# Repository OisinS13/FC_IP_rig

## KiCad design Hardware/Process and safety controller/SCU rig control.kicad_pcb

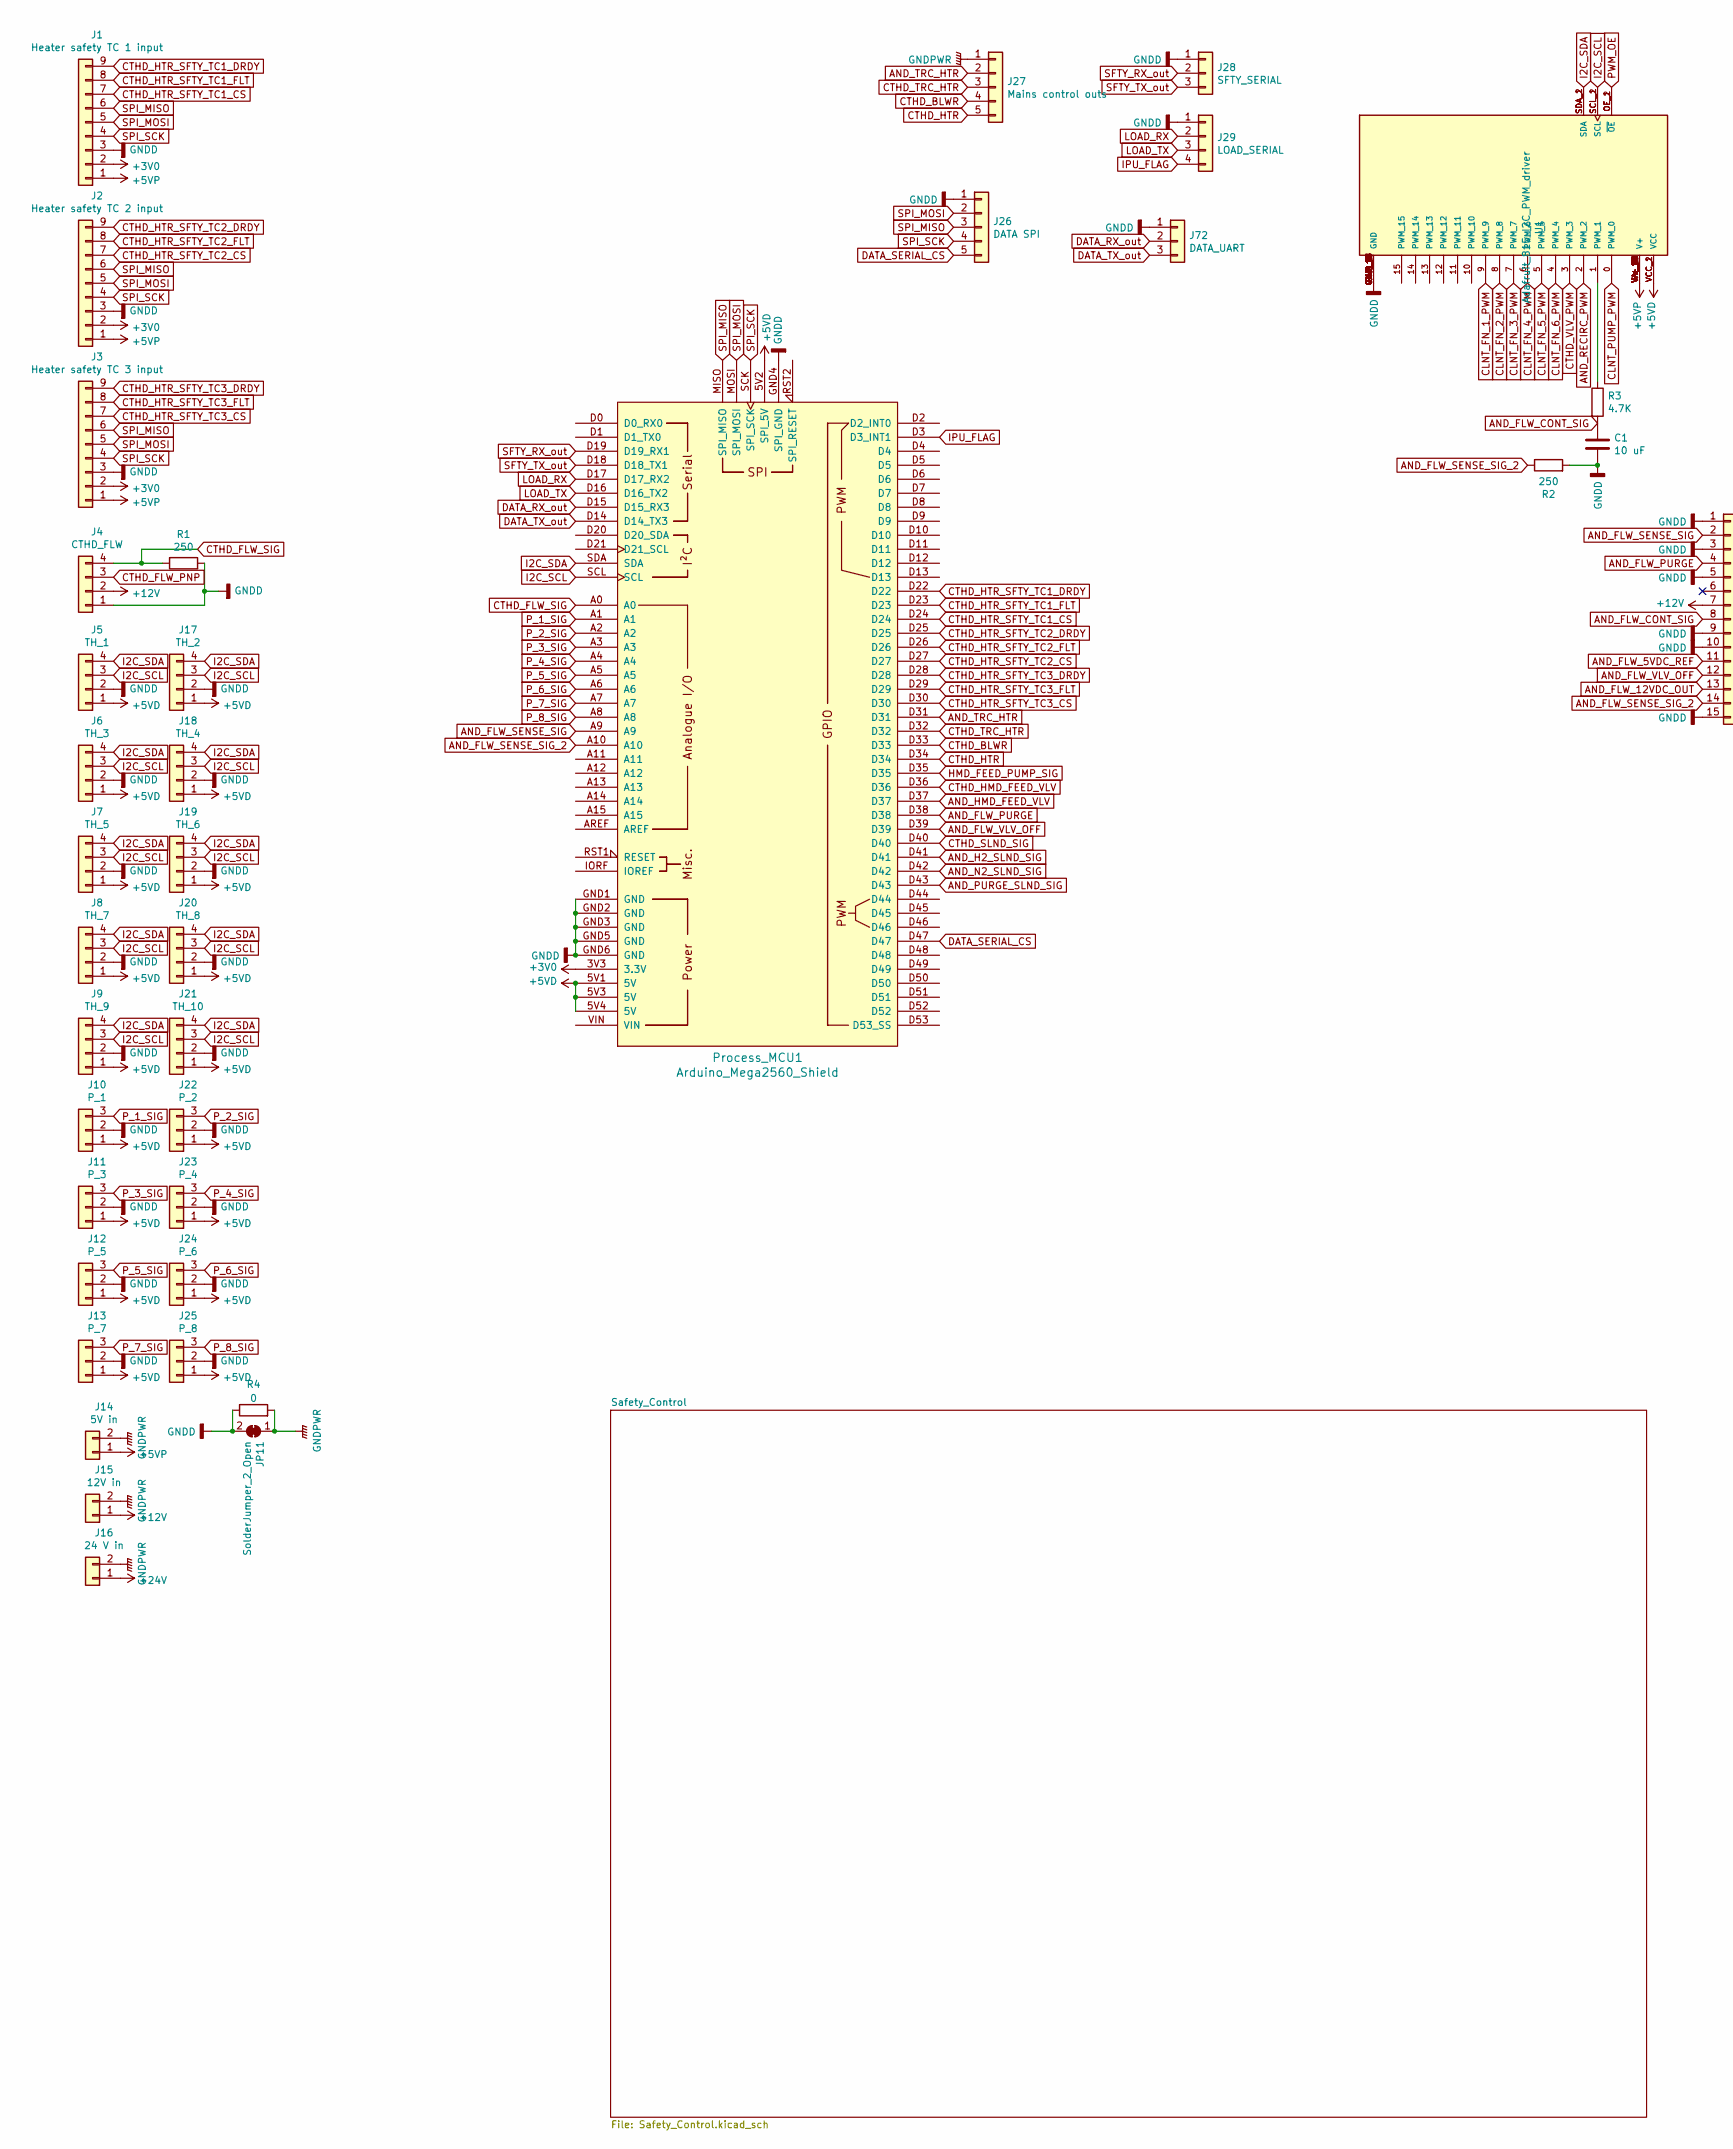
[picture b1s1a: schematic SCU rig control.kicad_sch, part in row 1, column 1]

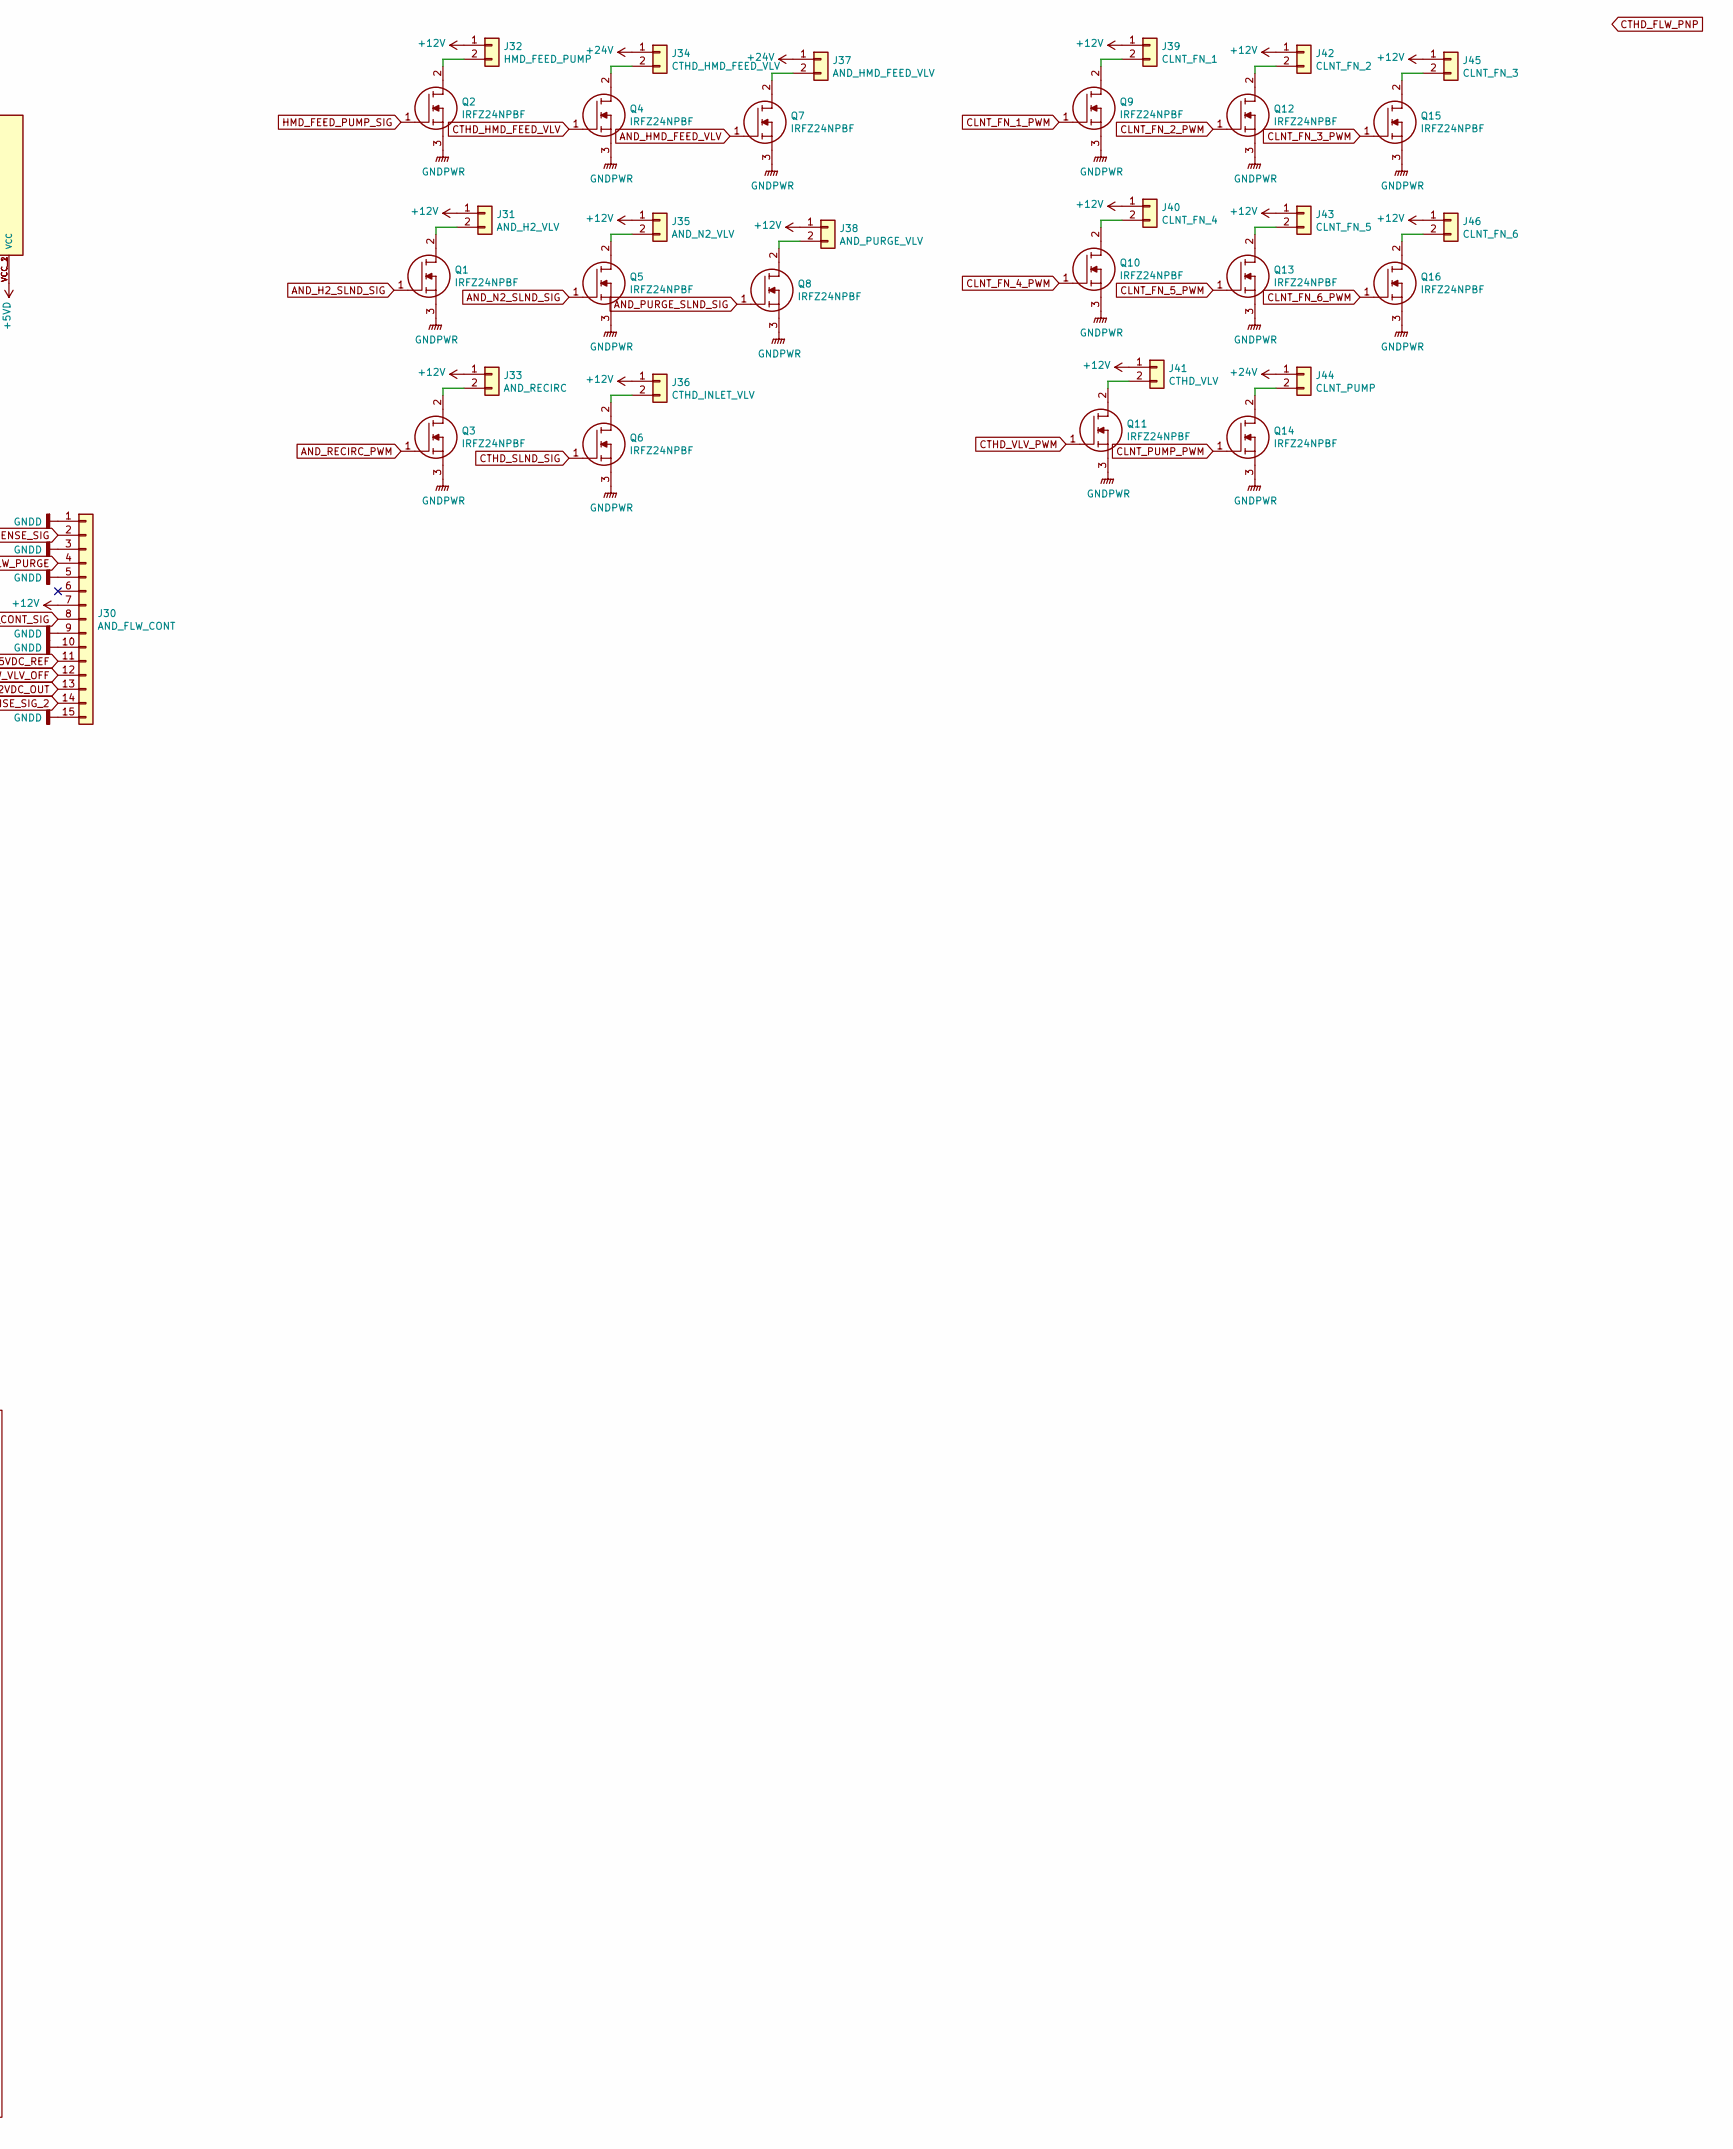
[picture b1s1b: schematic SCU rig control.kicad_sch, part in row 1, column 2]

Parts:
C1: 10 uF; CP_Radial_D5.0mm_P2.00mm
J1: Heater safety TC 1 input; Adafruit_3263
J2: Heater safety TC 2 input; Adafruit_3263
J3: Heater safety TC 3 input; Adafruit_3263
J4: CTHD_FLW; 1963557
J5: TH_1; 1963557
J6: TH_3; 1963557
J7: TH_5; 1963557
J8: TH_7; 1963557
J9: TH_9; 1963557
J10: P_1; 1963544
J11: P_3; 1963544
J12: P_5; 1963544
J13: P_7; 1963544
J14: 5V in; 1963531
J15: 12V in; SolderWirePad_1x02_P7.62mm_Drill2.5mm
J16: 24 V in; SolderWirePad_1x02_P7.62mm_Drill2.5mm
J17: TH_2; 1963557
J18: TH_4; 1963557
J19: TH_6; 1963557
J20: TH_8; 1963557
J21: TH_10; 1963557
J22: P_2; 1963544
J23: P_4; 1963544
J24: P_6; 1963544
J25: P_8; 1963544
J26: DATA SPI; 1881587
J27: Mains control outs; 1881587
J28: SFTY_SERIAL; 1963544
J29: LOAD_SERIAL; 1963557
J30: AND_FLW_CONT; DSUB-15_Male_Vertical_P2.77x2.84mm
J31: AND_H2_VLV; 1963531
J32: HMD_FEED_PUMP; 1963531
J33: AND_RECIRC; 1963531
J34: CTHD_HMD_FEED_VLV; 1963531
J35: AND_N2_VLV; 1963531
J36: CTHD_INLET_VLV; 1963531
J37: AND_HMD_FEED_VLV; 1963531
J38: AND_PURGE_VLV; 1963531
J39: CLNT_FN_1; 1963531
J40: CLNT_FN_4; 1963531
J41: CTHD_VLV; 1963531
J42: CLNT_FN_2; 1963531
J43: CLNT_FN_5; 1963531
J44: CLNT_PUMP; 1963531
J45: CLNT_FN_3; 1963531
J46: CLNT_FN_6; 1963531
J72: DATA_UART; 1963544
JP11: SolderJumper_2_Open; SolderJumper-2_P1.3mm_Bridged2Bar_RoundedPad1.0x1.5mm
Process_MCU1: Arduino_Mega2560_Shield
Q1, Q2, Q3, Q4, Q5, Q6, Q7, Q8, Q9, Q10, Q11, Q12, Q13, Q14, Q15, Q16: IRFZ24NPBF; TO254P469X1042X1967-3P; Mouser Part Number 942-IRFZ24NPBF
R1, R2: 250; R_Axial_DIN0411_L9.9mm_D3.6mm_P15.24mm_Horizontal
R3: 4.7K; R_Axial_DIN0411_L9.9mm_D3.6mm_P15.24mm_Horizontal
R4: 0; R_Axial_DIN0411_L9.9mm_D3.6mm_P15.24mm_Horizontal
U1: Adafruit_815_I2C_PWM_driver; MODULE_815

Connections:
+3V0: J1.2, J2.2, J3.2, Process_MCU1.3V3 (3.3V)
+5VD: J5.1, J6.1, J7.1, J8.1, J9.1, J10.1, J11.1, J12.1, J13.1, J17.1, J18.1, J19.1, J20.1, J21.1, J22.1, J23.1, J24.1, J25.1, Process_MCU1.5V1 (5V), Process_MCU1.5V2 (SPI_5V), Process_MCU1.5V3 (5V), Process_MCU1.5V4 (5V), U1.VCC_1 (VCC), U1.VCC_2 (VCC)
+5VP: J1.1, J2.1, J3.1, J14.1, U1.V+_1 (V+), U1.V+_2 (V+), U1.V+_3 (V+), U1.V+_4 (V+), U1.V+_5 (V+), U1.V+_6 (V+), U1.V+_7 (V+), U1.V+_8 (V+), U1.V+_9 (V+), U1.V+_10 (V+), U1.V+_11 (V+), U1.V+_12 (V+), U1.V+_13 (V+), U1.V+_14 (V+), U1.V+_15 (V+), U1.V+_16 (V+), U1.V+_17 (V+), U1.V+_18 (V+)
+12V: J4.2, J15.1, J30.7, J31.1, J32.1, J33.1, J35.1, J36.1, J38.1, J39.1, J40.1, J41.1, J42.1, J43.1, J45.1, J46.1
+24V: J16.1, J34.1, J37.1, J44.1
AND_FLW_5VDC_REF: J30.11
AND_FLW_12VDC_OUT: J30.13
AND_FLW_CONT_SIG: C1.1, J30.8, R3.2
AND_FLW_PURGE: J30.4, Process_MCU1.D38
AND_FLW_SENSE_SIG: J30.2, Process_MCU1.A9
AND_FLW_SENSE_SIG_2: J30.14, Process_MCU1.A10, R2.1
AND_FLW_VLV_OFF: J30.12, Process_MCU1.D39
AND_H2_SLND_SIG: Process_MCU1.D41, Q1.1
AND_HMD_FEED_VLV: Process_MCU1.D37, Q7.1
AND_N2_SLND_SIG: Process_MCU1.D42, Q5.1
AND_PURGE_SLND_SIG: Process_MCU1.D43, Q8.1
AND_RECIRC_PWM: Q3.1, U1.2 (PWM_2)
AND_TRC_HTR: J27.2, Process_MCU1.D31
CLNT_FN_1_PWM: Q9.1, U1.9 (PWM_9)
CLNT_FN_2_PWM: Q12.1, U1.8 (PWM_8)
CLNT_FN_3_PWM: Q15.1, U1.7 (PWM_7)
CLNT_FN_4_PWM: Q10.1, U1.6 (PWM_6)
CLNT_FN_5_PWM: Q13.1, U1.5 (PWM_5)
CLNT_FN_6_PWM: Q16.1, U1.4 (PWM_4)
CLNT_PUMP_PWM: Q14.1, U1.0 (PWM_0)
CTHD_BLWR: J27.4, Process_MCU1.D33
CTHD_FLW_PNP: J4.3
CTHD_FLW_SIG: J4.4, Process_MCU1.A0, R1.2
CTHD_HMD_FEED_VLV: Process_MCU1.D36, Q4.1
CTHD_HTR: J27.5, Process_MCU1.D34
CTHD_HTR_SFTY_TC1_CS: J1.7, Process_MCU1.D24
CTHD_HTR_SFTY_TC1_DRDY: J1.9, Process_MCU1.D22
CTHD_HTR_SFTY_TC1_FLT: J1.8, Process_MCU1.D23
CTHD_HTR_SFTY_TC2_CS: J2.7, Process_MCU1.D27
CTHD_HTR_SFTY_TC2_DRDY: J2.9, Process_MCU1.D25
CTHD_HTR_SFTY_TC2_FLT: J2.8, Process_MCU1.D26
CTHD_HTR_SFTY_TC3_CS: J3.7, Process_MCU1.D30
CTHD_HTR_SFTY_TC3_DRDY: J3.9, Process_MCU1.D28
CTHD_HTR_SFTY_TC3_FLT: J3.8, Process_MCU1.D29
CTHD_SLND_SIG: Process_MCU1.D40, Q6.1
CTHD_TRC_HTR: J27.3, Process_MCU1.D32
CTHD_VLV_PWM: Q11.1, U1.3 (PWM_3)
DATA_RX_out: J72.2, Process_MCU1.D15 (D15_RX3)
DATA_SERIAL_CS: J26.5, Process_MCU1.D47
DATA_TX_out: J72.3, Process_MCU1.D14 (D14_TX3)
GNDD: C1.2, J1.3, J2.3, J3.3, J4.1, J5.2, J6.2, J7.2, J8.2, J9.2, J10.2, J11.2, J12.2, J13.2, J17.2, J18.2, J19.2, J20.2, J21.2, J22.2, J23.2, J24.2, J25.2, J26.1, J28.1, J29.1, J30.1, J30.3, J30.5, J30.9, J30.10, J30.15, J72.1, JP11.2 (B), Process_MCU1.GND1 (GND), Process_MCU1.GND2 (GND), Process_MCU1.GND3 (GND), Process_MCU1.GND4 (SPI_GND), Process_MCU1.GND5 (GND), Process_MCU1.GND6 (GND), R1.1, R2.2, R4.1, U1.GND_1 (GND), U1.GND_2 (GND), U1.GND_3 (GND), U1.GND_4 (GND), U1.GND_5 (GND), U1.GND_6 (GND), U1.GND_7 (GND), U1.GND_8 (GND), U1.GND_9 (GND), U1.GND_10 (GND), U1.GND_11 (GND), U1.GND_12 (GND), U1.GND_13 (GND), U1.GND_14 (GND), U1.GND_15 (GND), U1.GND_16 (GND), U1.GND_17 (GND), U1.GND_18 (GND)
GNDPWR: J14.2, J15.2, J16.2, J27.1, JP11.1 (A), Q1.3, Q2.3, Q3.3, Q4.3, Q5.3, Q6.3, Q7.3, Q8.3, Q9.3, Q10.3, Q11.3, Q12.3, Q13.3, Q14.3, Q15.3, Q16.3, R4.2
HMD_FEED_PUMP_SIG: Process_MCU1.D35, Q2.1
I2C_SCL: J5.3, J6.3, J7.3, J8.3, J9.3, J17.3, J18.3, J19.3, J20.3, J21.3, Process_MCU1.SCL, U1.SCL_1 (SCL), U1.SCL_2 (SCL)
I2C_SDA: J5.4, J6.4, J7.4, J8.4, J9.4, J17.4, J18.4, J19.4, J20.4, J21.4, Process_MCU1.SDA, U1.SDA_1 (SDA), U1.SDA_2 (SDA)
IPU_FLAG: J29.4, Process_MCU1.D3 (D3_INT1)
LOAD_RX: J29.2, Process_MCU1.D17 (D17_RX2)
LOAD_TX: J29.3, Process_MCU1.D16 (D16_TX2)
unnamed: J31.2, Q1.2
unnamed: J32.2, Q2.2
unnamed: J33.2, Q3.2
unnamed: J34.2, Q4.2
unnamed: J35.2, Q5.2
unnamed: J36.2, Q6.2
unnamed: J37.2, Q7.2
unnamed: J38.2, Q8.2
unnamed: J39.2, Q9.2
unnamed: J40.2, Q10.2
unnamed: J41.2, Q11.2
unnamed: J42.2, Q12.2
unnamed: J43.2, Q13.2
unnamed: J44.2, Q14.2
unnamed: J45.2, Q15.2
unnamed: J46.2, Q16.2
unnamed: R3.1, U1.1 (PWM_1)
PWM_OE: U1.OE_1 (~OE), U1.OE_2 (~OE)
P_1_SIG: J10.3, Process_MCU1.A1
P_2_SIG: J22.3, Process_MCU1.A2
P_3_SIG: J11.3, Process_MCU1.A3
P_4_SIG: J23.3, Process_MCU1.A4
P_5_SIG: J12.3, Process_MCU1.A5
P_6_SIG: J24.3, Process_MCU1.A6
P_7_SIG: J13.3, Process_MCU1.A7
P_8_SIG: J25.3, Process_MCU1.A8
SFTY_RX_out: J28.2, Process_MCU1.D19 (D19_RX1)
SFTY_TX_out: J28.3, Process_MCU1.D18 (D18_TX1)
SPI_MISO: J1.6, J2.6, J3.6, J26.3, Process_MCU1.MISO (SPI_MISO)
SPI_MOSI: J1.5, J2.5, J3.5, J26.2, Process_MCU1.MOSI (SPI_MOSI)
SPI_SCK: J1.4, J2.4, J3.4, J26.4, Process_MCU1.SCK (SPI_SCK)

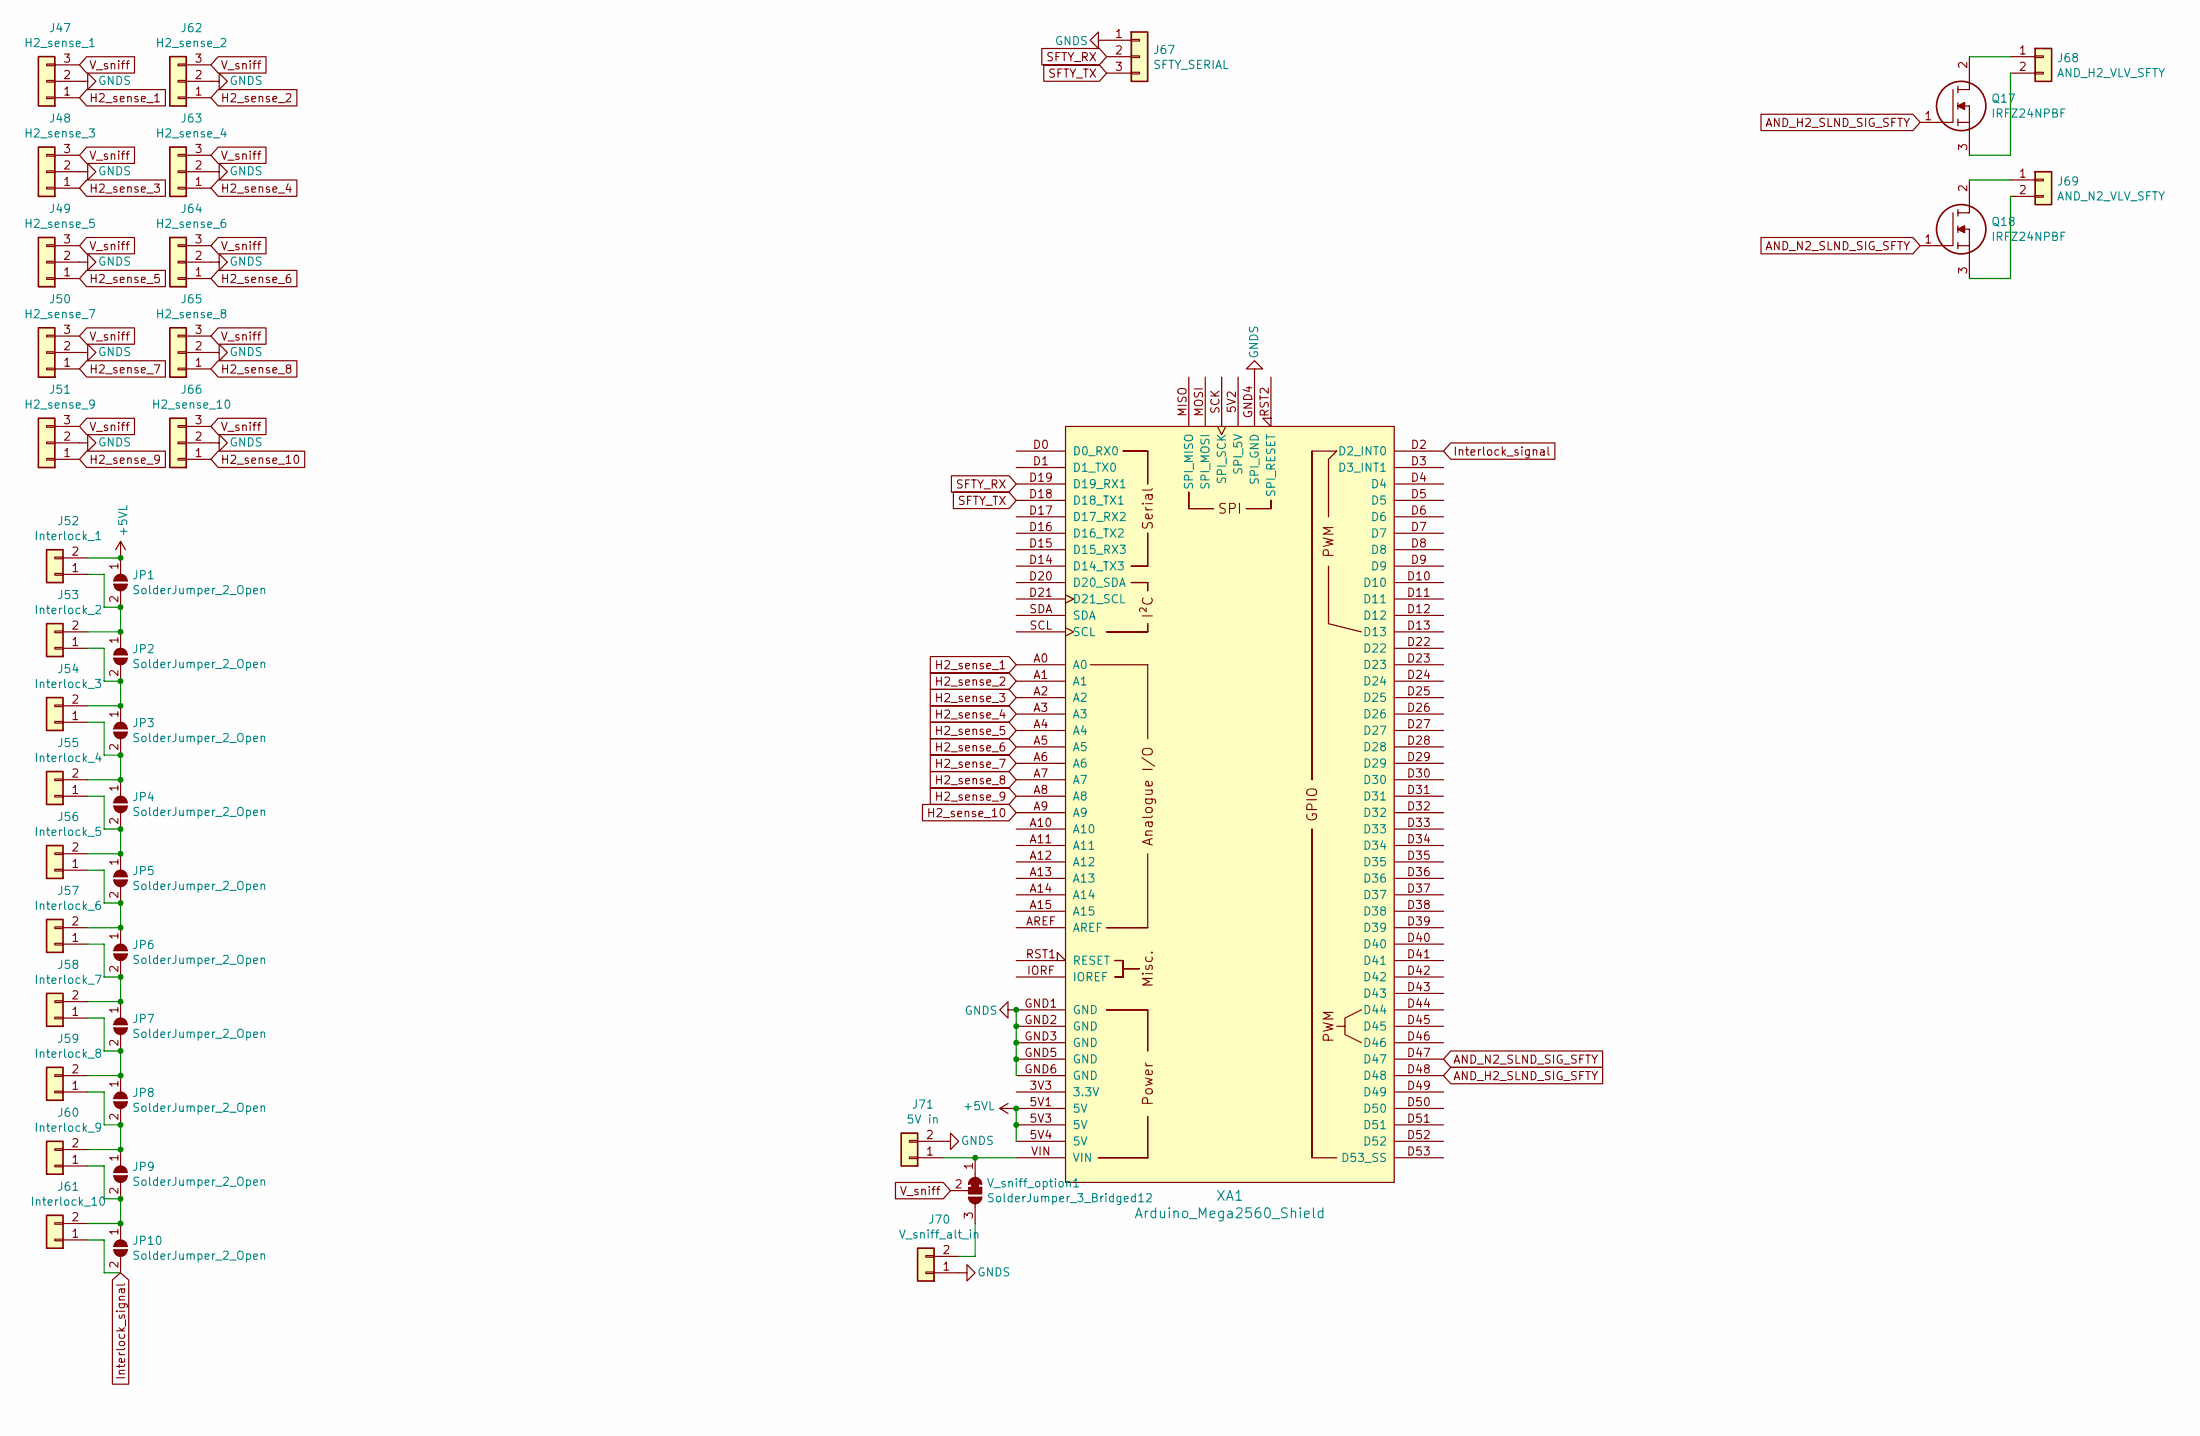
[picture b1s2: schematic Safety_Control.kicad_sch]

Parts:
J47: H2_sense_1; 1963544
J48: H2_sense_3; 1963544
J49: H2_sense_5; 1963544
J50: H2_sense_7; 1963544
J51: H2_sense_9; 1963544
J52: Interlock_1; 1963531
J53: Interlock_2; 1963531
J54: Interlock_3; 1963531
J55: Interlock_4; 1963531
J56: Interlock_5; 1963531
J57: Interlock_6; 1963531
J58: Interlock_7; 1963531
J59: Interlock_8; 1963531
J60: Interlock_9; 1963531
J61: Interlock_10; 1963531
J62: H2_sense_2; 1963544
J63: H2_sense_4; 1963544
J64: H2_sense_6; 1963544
J65: H2_sense_8; 1963544
J66: H2_sense_10; 1963544
J67: SFTY_SERIAL; 1963544
J68: AND_H2_VLV_SFTY; 1963531
J69: AND_N2_VLV_SFTY; 1963531
J70: V_sniff_alt_in; 1963531
J71: 5V in; 1963531
JP1, JP2, JP3, JP4, JP5, JP6, JP7, JP8, JP9, JP10: SolderJumper_2_Open; SolderJumper-2_P1.3mm_Open_RoundedPad1.0x1.5mm
Q17, Q18: IRFZ24NPBF; TO254P469X1042X1967-3P; Mouser Part Number 942-IRFZ24NPBF
V_sniff_option1: SolderJumper_3_Bridged12; SolderJumper-3_P1.3mm_Bridged12_RoundedPad1.0x1.5mm
XA1: Arduino_Mega2560_Shield

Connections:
+5VL: J52.2, JP1.1 (A), XA1.5V1 (5V), XA1.5V3 (5V), XA1.5V4 (5V)
AND_H2_SLND_SIG_SFTY: Q17.1, XA1.D48
AND_N2_SLND_SIG_SFTY: Q18.1, XA1.D47
GNDS: J47.2, J48.2, J49.2, J50.2, J51.2, J62.2, J63.2, J64.2, J65.2, J66.2, J67.1, J70.1, J71.2, XA1.GND1 (GND), XA1.GND2 (GND), XA1.GND3 (GND), XA1.GND4 (SPI_GND), XA1.GND5 (GND), XA1.GND6 (GND)
H2_sense_1: J47.1, XA1.A0
H2_sense_2: J62.1, XA1.A1
H2_sense_3: J48.1, XA1.A2
H2_sense_4: J63.1, XA1.A3
H2_sense_5: J49.1, XA1.A4
H2_sense_6: J64.1, XA1.A5
H2_sense_7: J50.1, XA1.A6
H2_sense_8: J65.1, XA1.A7
H2_sense_9: J51.1, XA1.A8
H2_sense_10: J66.1, XA1.A9
Interlock_signal: J61.1, JP10.2 (B), XA1.D2 (D2_INT0)
unnamed: J52.1, J53.2, JP1.2 (B), JP2.1 (A)
unnamed: J53.1, J54.2, JP2.2 (B), JP3.1 (A)
unnamed: J54.1, J55.2, JP3.2 (B), JP4.1 (A)
unnamed: J55.1, J56.2, JP4.2 (B), JP5.1 (A)
unnamed: J56.1, J57.2, JP5.2 (B), JP6.1 (A)
unnamed: J57.1, J58.2, JP6.2 (B), JP7.1 (A)
unnamed: J58.1, J59.2, JP7.2 (B), JP8.1 (A)
unnamed: J59.1, J60.2, JP8.2 (B), JP9.1 (A)
unnamed: J60.1, J61.2, JP9.2 (B), JP10.1 (A)
unnamed: J68.1, Q17.2
unnamed: J68.2, Q17.3
unnamed: J69.1, Q18.2
unnamed: J69.2, Q18.3
unnamed: J70.2, V_sniff_option1.3 (B)
unnamed: J71.1, V_sniff_option1.1 (A), XA1.VIN
SFTY_RX: J67.2, XA1.D19 (D19_RX1)
SFTY_TX: J67.3, XA1.D18 (D18_TX1)
V_sniff: J47.3, J48.3, J49.3, J50.3, J51.3, J62.3, J63.3, J64.3, J65.3, J66.3, V_sniff_option1.2 (C)

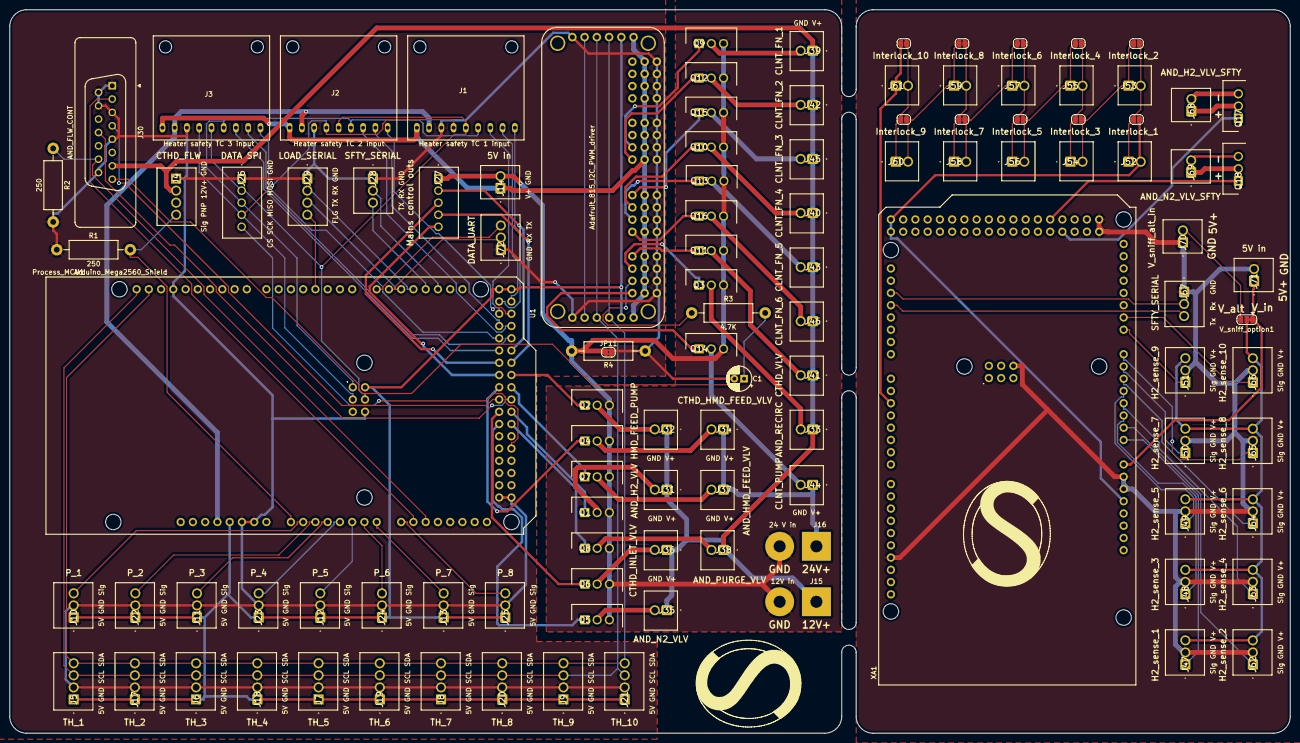
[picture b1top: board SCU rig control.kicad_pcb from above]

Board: 2 copper layers, 265.5 x 150.0 mm, 110 parts (0 on the bottom side), 114 nets.

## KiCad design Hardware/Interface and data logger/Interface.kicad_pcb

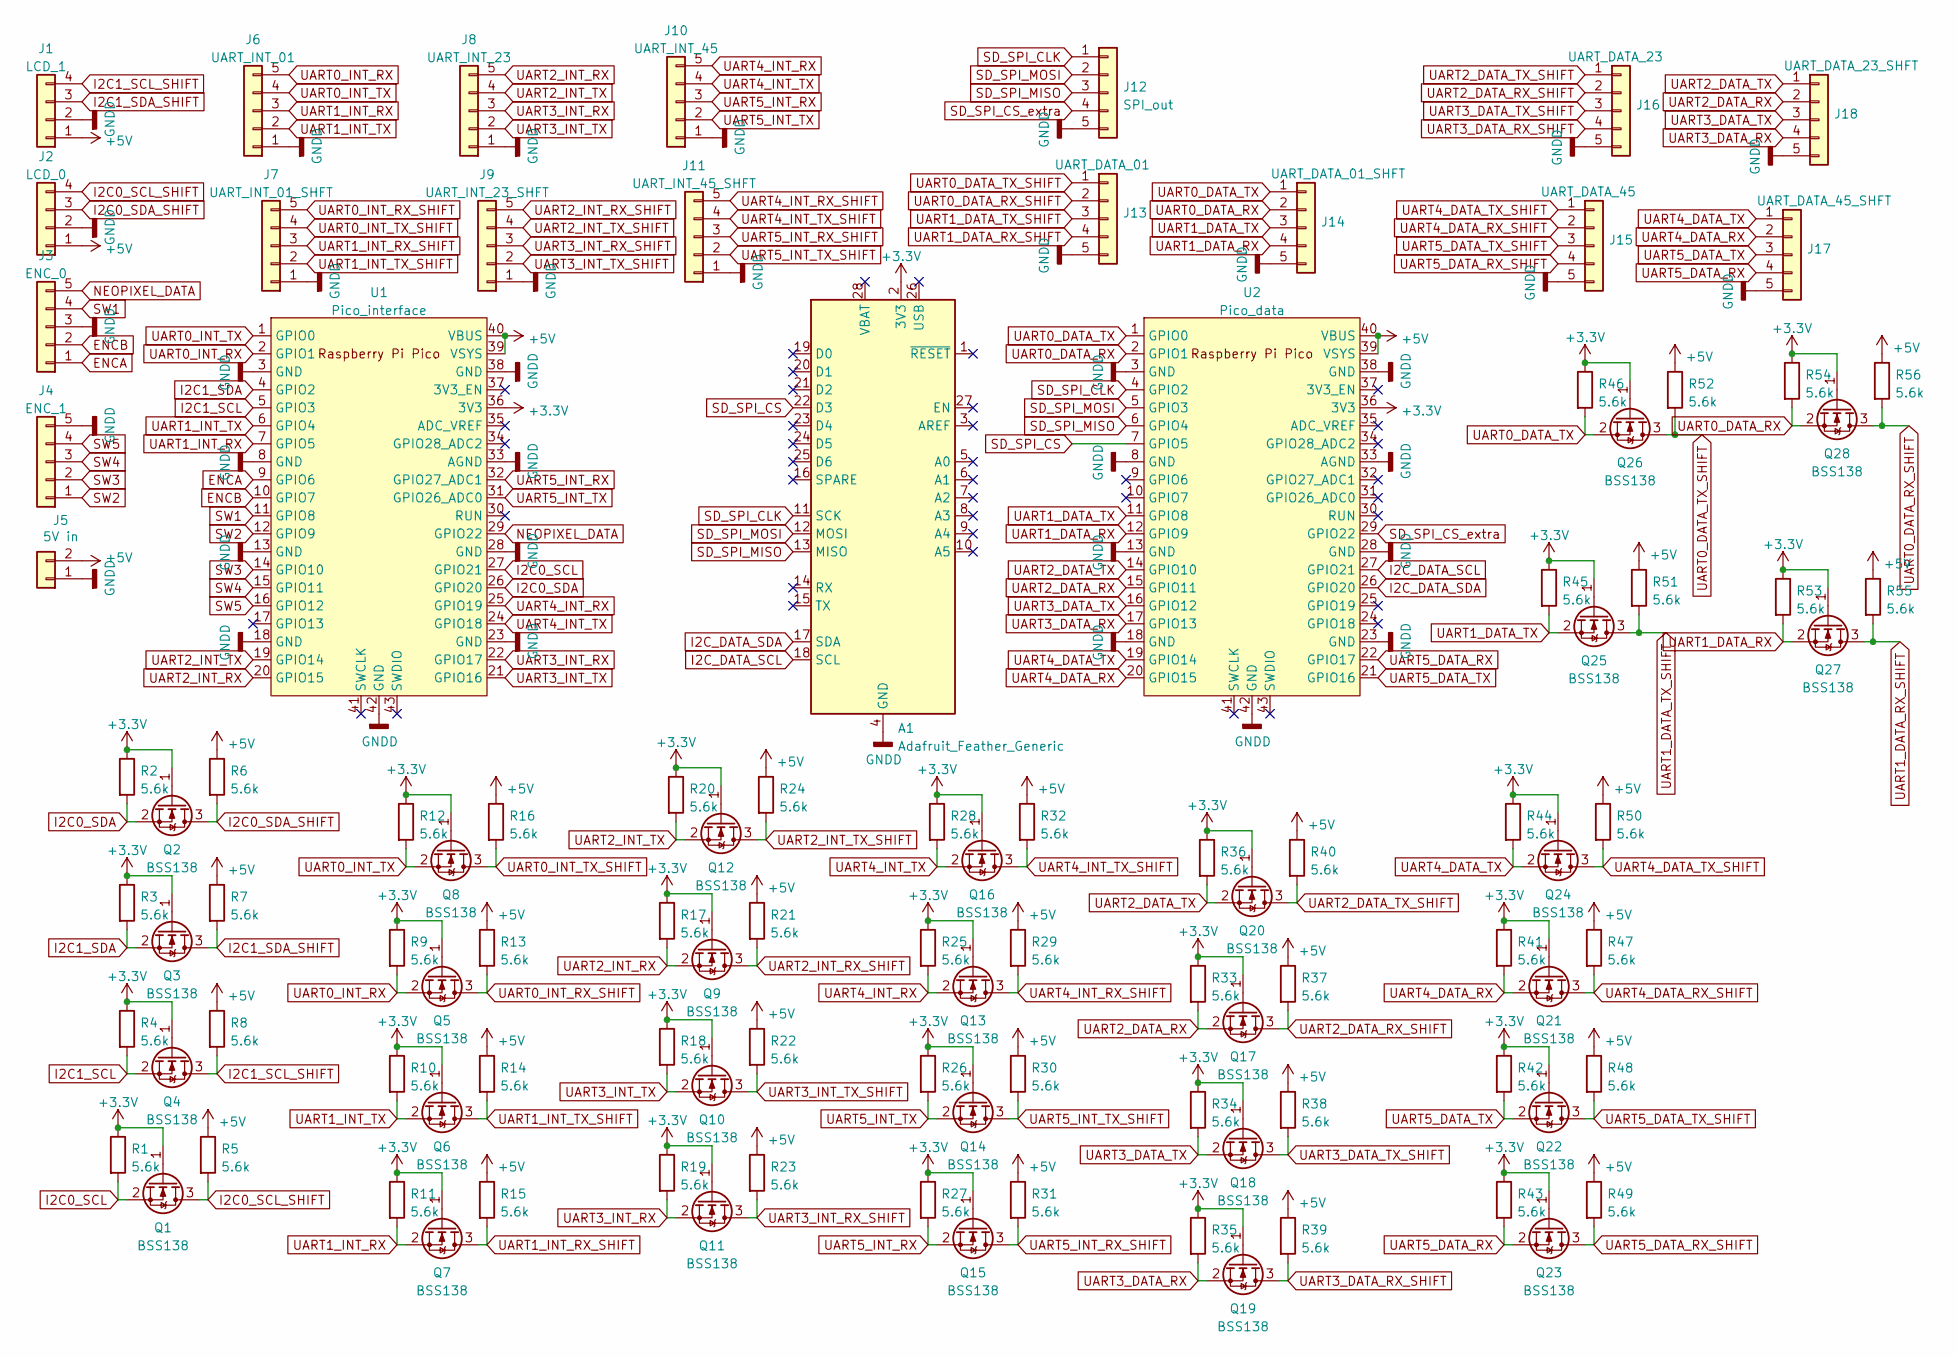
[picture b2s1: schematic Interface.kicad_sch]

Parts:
A1: Adafruit_Feather_Generic; Adafruit_Feather
J1: LCD_1; 1963557
J2: LCD_0; 1963557
J3: ENC_0; 1881587
J4: ENC_1; 1881587
J5: 5V in; 1963531
J6: UART_INT_01; 1881587
J7: UART_INT_01_SHFT; 1881587
J8: UART_INT_23; 1881587
J9: UART_INT_23_SHFT; 1881587
J10: UART_INT_45; 1881587
J11: UART_INT_45_SHFT; 1881587
J12: SPI_out; 1881587
J13: UART_DATA_01; 1881587
J14: UART_DATA_01_SHFT; 1881587
J15: UART_DATA_45; 1881587
J16: UART_DATA_23; 1881587
J17: UART_DATA_45_SHFT; 1881587
J18: UART_DATA_23_SHFT; 1881587
Q1, Q2, Q3, Q4, Q5, Q6, Q7, Q8, Q9, Q10, Q11, Q12, Q13, Q14, Q15, Q16, Q17, Q18, Q19, Q20, Q21, Q22, Q23, Q24, Q25, Q26, Q27, Q28: BSS138; SOT-23
R1, R2, R3, R4, R5, R6, R7, R8, R9, R10, R11, R12, R13, R14, R15, R16, R17, R18, R19, R20, R21, R22, R23, R24, R25, R26, R27, R28, R29, R30, R31, R32, R33, R34, R35, R36, R37, R38, R39, R40, R41, R42, R43, R44, R45, R46, R47, R48, R49, R50, R51, R52, R53, R54, R55, R56: 5.6k; R_0603_1608Metric_Pad0.98x0.95mm_HandSolder
U1: Pico_interface; RPi_Pico_SMD_TH
U2: Pico_data; RPi_Pico_SMD_TH

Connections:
+3.3V: A1.2 (3V3), Q1.1 (G), Q2.1 (G), Q3.1 (G), Q4.1 (G), Q5.1 (G), Q6.1 (G), Q7.1 (G), Q8.1 (G), Q9.1 (G), Q10.1 (G), Q11.1 (G), Q12.1 (G), Q13.1 (G), Q14.1 (G), Q15.1 (G), Q16.1 (G), Q17.1 (G), Q18.1 (G), Q19.1 (G), Q20.1 (G), Q21.1 (G), Q22.1 (G), Q23.1 (G), Q24.1 (G), Q25.1 (G), Q26.1 (G), Q27.1 (G), Q28.1 (G), R1.1, R2.1, R3.1, R4.1, R9.1, R10.1, R11.1, R12.1, R17.1, R18.1, R19.1, R20.1, R25.1, R26.1, R27.1, R28.1, R33.1, R34.1, R35.1, R36.1, R41.1, R42.1, R43.1, R44.1, R45.1, R46.1, R53.1, R54.1, U1.36 (3V3), U2.36 (3V3)
+5V: J1.1, J2.1, J5.2, R5.1, R6.1, R7.1, R8.1, R13.1, R14.1, R15.1, R16.1, R21.1, R22.1, R23.1, R24.1, R29.1, R30.1, R31.1, R32.1, R37.1, R38.1, R39.1, R40.1, R47.1, R48.1, R49.1, R50.1, R51.1, R52.1, R55.1, R56.1, U1.39 (VSYS), U1.40 (VBUS), U2.39 (VSYS), U2.40 (VBUS)
ENCA: J3.1, U1.9 (GPIO6)
ENCB: J3.2, U1.10 (GPIO7)
GNDD: A1.4 (GND), J1.2, J2.2, J3.3, J4.5, J5.1, J6.1, J7.1, J8.1, J9.1, J10.1, J11.1, J12.5, J13.5, J14.5, J15.5, J16.5, J17.5, J18.5, U1.3 (GND), U1.8 (GND), U1.13 (GND), U1.18 (GND), U1.23 (GND), U1.28 (GND), U1.33 (AGND), U1.38 (GND), U1.42 (GND), U2.3 (GND), U2.8 (GND), U2.13 (GND), U2.18 (GND), U2.23 (GND), U2.28 (GND), U2.33 (AGND), U2.38 (GND), U2.42 (GND)
I2C0_SCL: Q1.2 (S), R1.2, U1.27 (GPIO21)
I2C0_SCL_SHIFT: J2.4, Q1.3 (D), R5.2
I2C0_SDA: Q2.2 (S), R2.2, U1.26 (GPIO20)
I2C0_SDA_SHIFT: J2.3, Q2.3 (D), R6.2
I2C1_SCL: Q4.2 (S), R4.2, U1.5 (GPIO3)
I2C1_SCL_SHIFT: J1.4, Q4.3 (D), R8.2
I2C1_SDA: Q3.2 (S), R3.2, U1.4 (GPIO2)
I2C1_SDA_SHIFT: J1.3, Q3.3 (D), R7.2
I2C_DATA_SCL: A1.18 (SCL), U2.27 (GPIO21)
I2C_DATA_SDA: A1.17 (SDA), U2.26 (GPIO20)
NEOPIXEL_DATA: J3.5, U1.29 (GPIO22)
SD_SPI_CLK: A1.11 (SCK), J12.1, U2.4 (GPIO2)
SD_SPI_CS: A1.22 (D3), U2.7 (GPIO5)
SD_SPI_CS_extra: J12.4, U2.29 (GPIO22)
SD_SPI_MISO: A1.13 (MISO), J12.3, U2.6 (GPIO4)
SD_SPI_MOSI: A1.12 (MOSI), J12.2, U2.5 (GPIO3)
SW1: J3.4, U1.11 (GPIO8)
SW2: J4.1, U1.12 (GPIO9)
SW3: J4.2, U1.14 (GPIO10)
SW4: J4.3, U1.15 (GPIO11)
SW5: J4.4, U1.16 (GPIO12)
UART0_DATA_RX: J14.2, Q28.2 (S), R54.2, U2.2 (GPIO1)
UART0_DATA_RX_SHIFT: J13.2, Q28.3 (D), R56.2
UART0_DATA_TX: J14.1, Q26.2 (S), R46.2, U2.1 (GPIO0)
UART0_DATA_TX_SHIFT: J13.1, Q26.3 (D), R52.2
UART0_INT_RX: J6.5, Q5.2 (S), R9.2, U1.2 (GPIO1)
UART0_INT_RX_SHIFT: J7.5, Q5.3 (D), R13.2
UART0_INT_TX: J6.4, Q8.2 (S), R12.2, U1.1 (GPIO0)
UART0_INT_TX_SHIFT: J7.4, Q8.3 (D), R16.2
UART1_DATA_RX: J14.4, Q27.2 (S), R53.2, U2.12 (GPIO9)
UART1_DATA_RX_SHIFT: J13.4, Q27.3 (D), R55.2
UART1_DATA_TX: J14.3, Q25.2 (S), R45.2, U2.11 (GPIO8)
UART1_DATA_TX_SHIFT: J13.3, Q25.3 (D), R51.2
UART1_INT_RX: J6.3, Q7.2 (S), R11.2, U1.7 (GPIO5)
UART1_INT_RX_SHIFT: J7.3, Q7.3 (D), R15.2
UART1_INT_TX: J6.2, Q6.2 (S), R10.2, U1.6 (GPIO4)
UART1_INT_TX_SHIFT: J7.2, Q6.3 (D), R14.2
UART2_DATA_RX: J18.2, Q17.2 (S), R33.2, U2.15 (GPIO11)
UART2_DATA_RX_SHIFT: J16.2, Q17.3 (D), R37.2
UART2_DATA_TX: J18.1, Q20.2 (S), R36.2, U2.14 (GPIO10)
UART2_DATA_TX_SHIFT: J16.1, Q20.3 (D), R40.2
UART2_INT_RX: J8.5, Q9.2 (S), R17.2, U1.20 (GPIO15)
UART2_INT_RX_SHIFT: J9.5, Q9.3 (D), R21.2
UART2_INT_TX: J8.4, Q12.2 (S), R20.2, U1.19 (GPIO14)
UART2_INT_TX_SHIFT: J9.4, Q12.3 (D), R24.2
UART3_DATA_RX: J18.4, Q19.2 (S), R35.2, U2.17 (GPIO13)
UART3_DATA_RX_SHIFT: J16.4, Q19.3 (D), R39.2
UART3_DATA_TX: J18.3, Q18.2 (S), R34.2, U2.16 (GPIO12)
UART3_DATA_TX_SHIFT: J16.3, Q18.3 (D), R38.2
UART3_INT_RX: J8.3, Q11.2 (S), R19.2, U1.22 (GPIO17)
UART3_INT_RX_SHIFT: J9.3, Q11.3 (D), R23.2
UART3_INT_TX: J8.2, Q10.2 (S), R18.2, U1.21 (GPIO16)
UART3_INT_TX_SHIFT: J9.2, Q10.3 (D), R22.2
UART4_DATA_RX: J17.2, Q21.2 (S), R41.2, U2.20 (GPIO15)
UART4_DATA_RX_SHIFT: J15.2, Q21.3 (D), R47.2
UART4_DATA_TX: J17.1, Q24.2 (S), R44.2, U2.19 (GPIO14)
UART4_DATA_TX_SHIFT: J15.1, Q24.3 (D), R50.2
UART4_INT_RX: J10.5, Q13.2 (S), R25.2, U1.25 (GPIO19)
UART4_INT_RX_SHIFT: J11.5, Q13.3 (D), R29.2
UART4_INT_TX: J10.4, Q16.2 (S), R28.2, U1.24 (GPIO18)
UART4_INT_TX_SHIFT: J11.4, Q16.3 (D), R32.2
UART5_DATA_RX: J17.4, Q23.2 (S), R43.2, U2.22 (GPIO17)
UART5_DATA_RX_SHIFT: J15.4, Q23.3 (D), R49.2
UART5_DATA_TX: J17.3, Q22.2 (S), R42.2, U2.21 (GPIO16)
UART5_DATA_TX_SHIFT: J15.3, Q22.3 (D), R48.2
UART5_INT_RX: J10.3, Q15.2 (S), R27.2, U1.32 (GPIO27_ADC1)
UART5_INT_RX_SHIFT: J11.3, Q15.3 (D), R31.2
UART5_INT_TX: J10.2, Q14.2 (S), R26.2, U1.31 (GPIO26_ADC0)
UART5_INT_TX_SHIFT: J11.2, Q14.3 (D), R30.2

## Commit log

2022-11-01 Added code for load controller
2022-11-01 Added load control code
2022-11-18 Added load controller message types in messages.csv
2022-11-18 New load controller code
2022-11-28 data and msg transfer from and to load controller
2024-01-09 Deleted extra folders from bad commits
